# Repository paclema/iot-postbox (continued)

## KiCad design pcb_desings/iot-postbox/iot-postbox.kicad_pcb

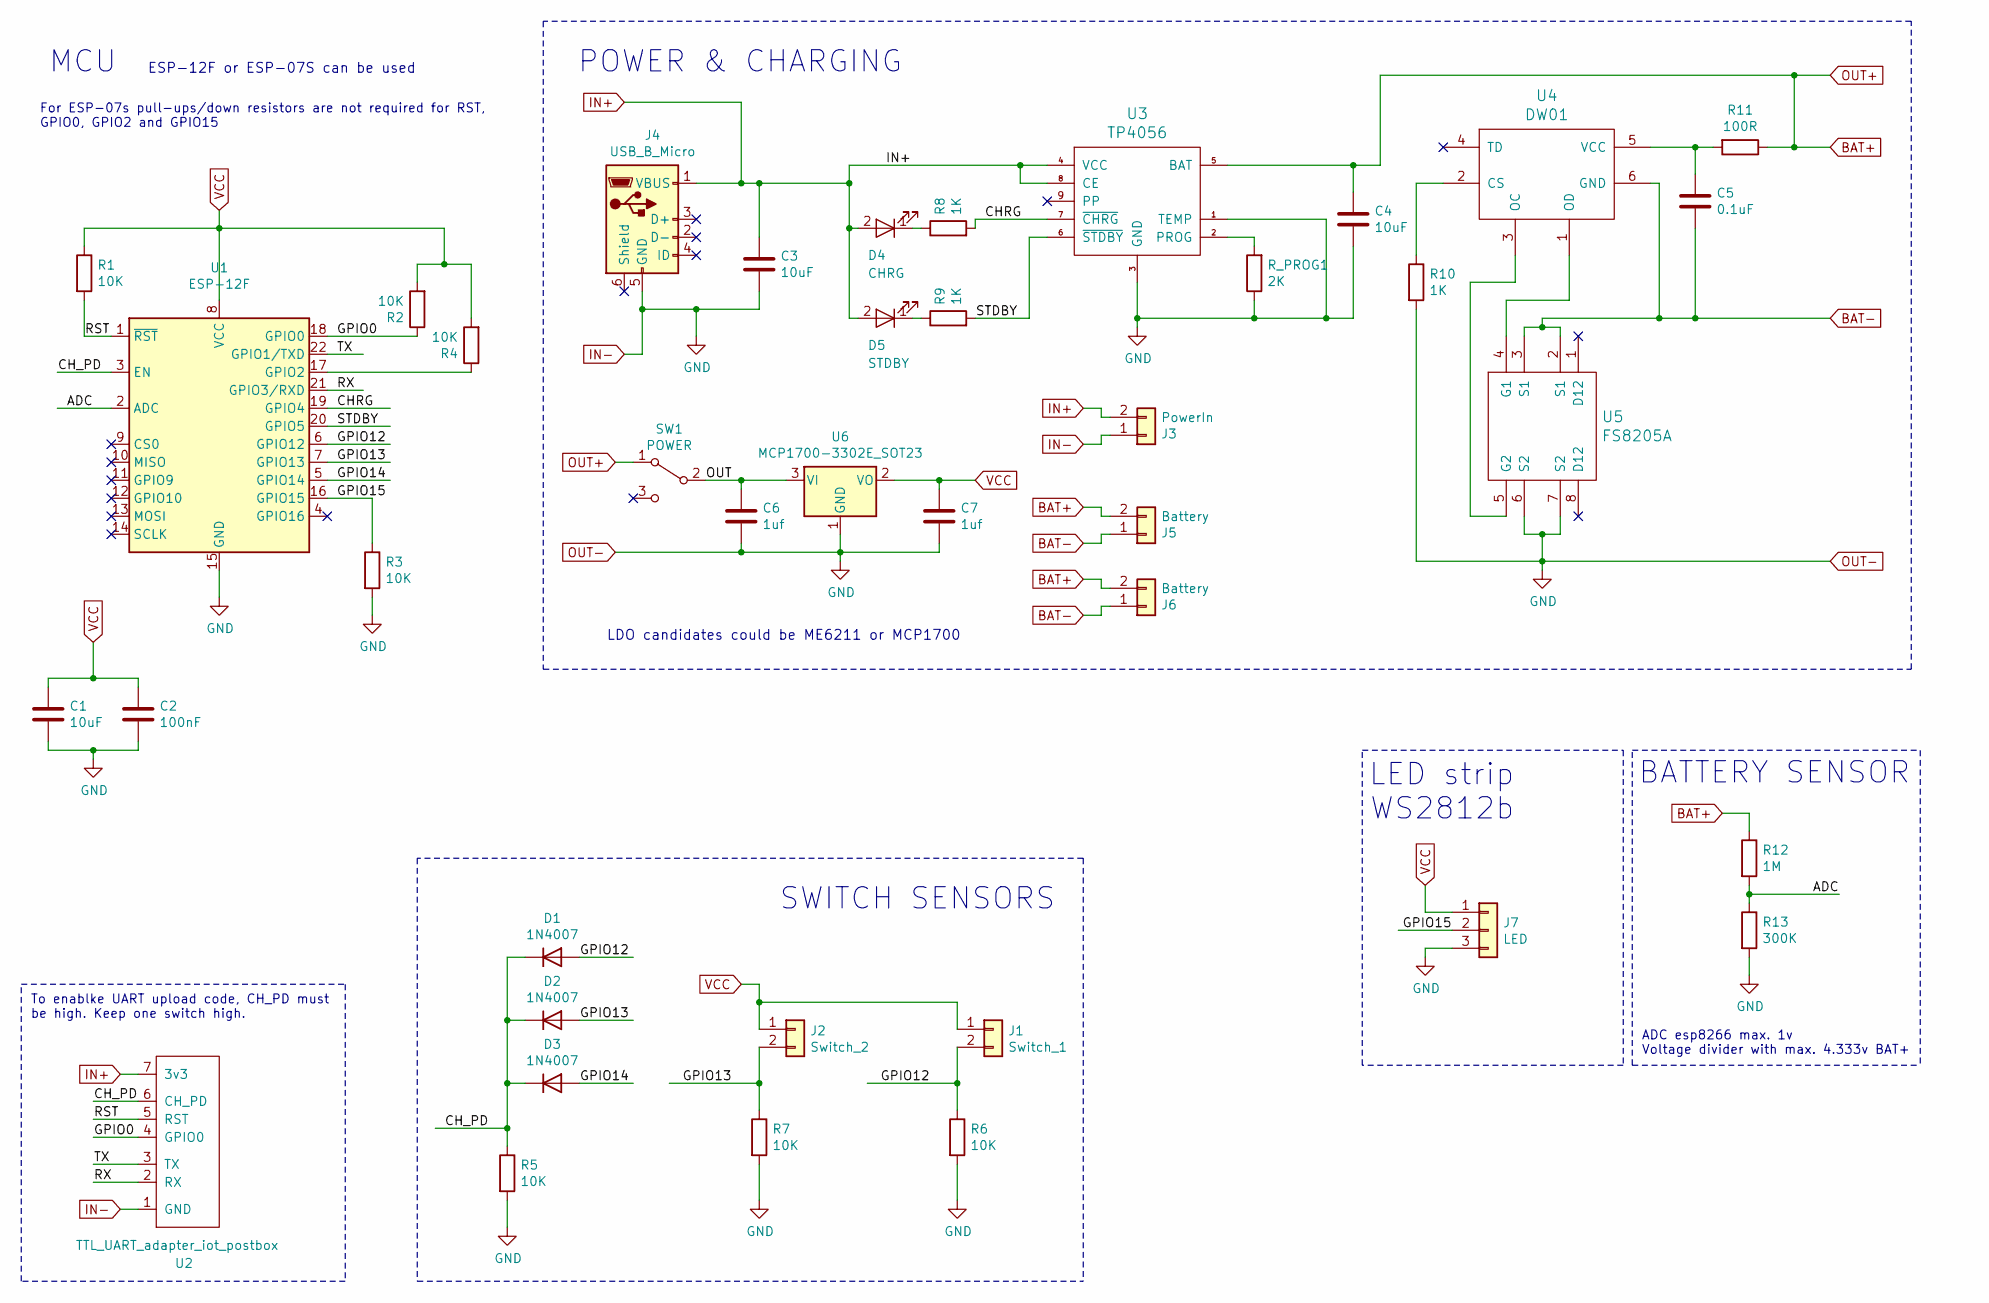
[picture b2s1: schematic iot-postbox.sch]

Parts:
C1, C3, C4: 10uF; C_0805_2012Metric
C2: 100nF; C_0805_2012Metric
C5: 0.1uF; C_0805_2012Metric
C6, C7: 1uf; C_0805_2012Metric
D1, D2, D3: 1N4007; D_SOD-123
D4: CHRG; LED_0805_2012Metric
D5: STDBY; LED_0805_2012Metric
J1: Switch_1; PinHeader_1x02_P2.54mm_Vertical
J2: Switch_2; PinHeader_1x02_P2.54mm_Vertical
J3: PowerIn; PinHeader_1x02_P2.54mm_Vertical
J4: USB_B_Micro; USB_Micro-B_Amphenol_10118194_Horizontal
J5: Battery; JST_PH_S2B-PH-SM4-TB_1x02-1MP_P2.00mm_Horizontal
J6: Battery; PinHeader_1x02_P2.54mm_Vertical
J7: LED; PinHeader_1x03_P2.54mm_Vertical
R1, R2, R3, R4, R5, R6, R7: 10K; R_0805_2012Metric
R8, R9, R10: 1K; R_0805_2012Metric
R11: 100R; R_0805_2012Metric
R12: 1M; R_0805_2012Metric
R13: 300K; R_0805_2012Metric
R_PROG1: 2K; R_0805_2012Metric
SW1: POWER; 1P2T_SPDT_MSK-C02_7pin
U1: ESP-12F; ESP-12E
U2: TTL_UART_adapter_iot_postbox; PinHeader_1x07_P2.54mm_Vertical
U3: TP4056; TP4056_SOP-8-PP
U4: DW01; SOT-23-6_Handsoldering
U5: FS8205A; TSSOP-8_4.4x3mm_P0.65mm
U6: MCP1700-3302E_SOT23; SOT-23

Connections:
/ADC: R12.2, R13.1, U1.2 (ADC)
/CHRG: R8.2, U1.19 (GPIO4), U3.7 (~CHRG)
/CH_PD: D1.1 (K), D2.1 (K), D3.1 (K), R5.1, U1.3 (EN), U2.6 (CH_PD)
/GPIO0: R2.1, U1.18 (GPIO0), U2.4 (GPIO0)
/GPIO12: D1.2 (A), J1.2, R6.1, U1.6 (GPIO12)
/GPIO13: D2.2 (A), J2.2, R7.1, U1.7 (GPIO13)
/GPIO14: D3.2 (A), U1.5 (GPIO14)
/GPIO15: J7.2, R3.1, U1.16 (GPIO15)
/OUT: C6.1, SW1.2 (B), U6.3 (VI)
/RST: R1.2, U1.1 (~RST), U2.5 (RST)
/RX: U1.21 (GPIO3/RXD), U2.2 (RX)
/STDBY: R9.2, U1.20 (GPIO5), U3.6 (~STDBY)
/TX: U1.22 (GPIO1/TXD), U2.3 (TX)
BAT+: C4.1, J5.2, J6.2, R11.1, R12.1, SW1.1 (A), U3.5 (BAT)
BAT-: C5.2, J5.1, J6.1, U4.6 (GND), U5.2 (S1), U5.3 (S1)
IN+: C3.1, D4.2 (A), D5.2 (A), J3.2, J4.1 (VBUS), U2.7 (3v3), U3.4 (VCC), U3.8 (CE)
IN-: C1.2, C2.2, C3.2, C4.2, C6.2, C7.2, J3.1, J4.5 (GND), J7.3, R3.2, R5.2, R6.2, R7.2, R10.2, R13.2, R_PROG1.1, U1.15 (GND), U2.1 (GND), U3.1 (TEMP), U3.3 (GND), U5.6 (S2), U5.7 (S2), U6.1 (GND)
unnamed: C5.1, R11.2, U4.5 (VCC)
unnamed: D4.1 (K), R8.1
unnamed: D5.1 (K), R9.1
unnamed: R4.1, U1.17 (GPIO2)
unnamed: R10.1, U4.2 (CS)
unnamed: R_PROG1.2, U3.2 (PROG)
unnamed: U4.1 (OD), U5.4 (G1)
unnamed: U4.3 (OC), U5.5 (G2)
VCC: C1.1, C2.1, C7.1, J1.1, J2.1, J7.1, R1.1, R2.2, R4.2, U1.8 (VCC), U6.2 (VO)

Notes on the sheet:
To enablke UART upload code, CH_PD must be high. Keep one switch high.
POWER & CHARGING
SWITCH SENSORS
MCU
ESP-12F or ESP-07S can be used
LDO candidates could be ME6211 or MCP1700
ADC esp8266 max. 1v Voltage divider with max. 4.333v BAT+
BATTERY SENSOR
For ESP-07s pull-ups/down resistors are not required for RST, GPIO0, GPIO2 and GPIO15
LED strip WS2812b

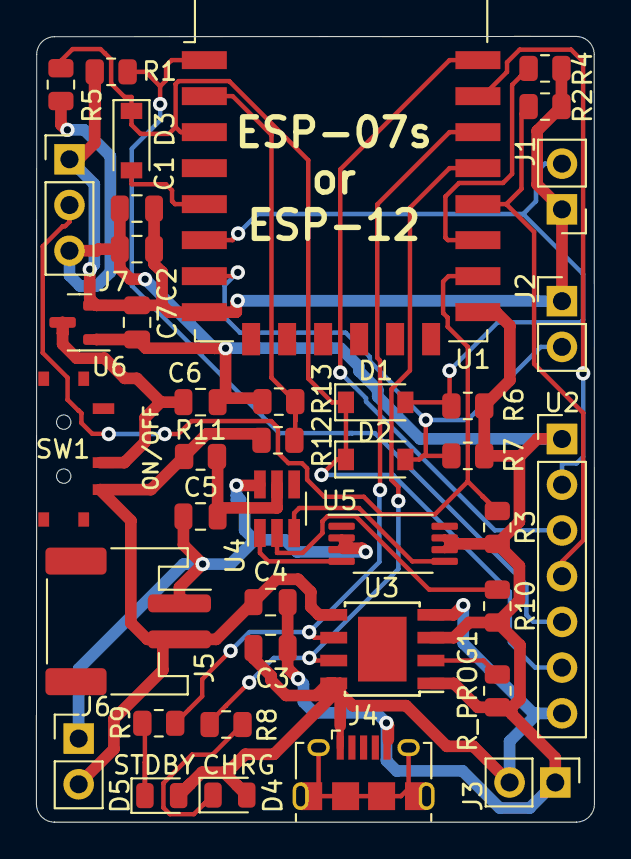
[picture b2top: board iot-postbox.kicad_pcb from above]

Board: 2 copper layers, 31.0 x 43.6 mm, 40 parts (0 on the bottom side), 26 nets.

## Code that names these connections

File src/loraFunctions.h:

#ifndef LoraFunctions_H
#define LoraFunctions_H
#pragma once

#include "Arduino.h"
#include <lmic.h>
#include <hal/hal.h>
#include <SPI.h>


// This EUI must be in little-endian format, so least-significant-byte
// first. When copying an EUI from ttnctl output, this means to reverse
// the bytes. For TTN issued EUIs the last bytes should be 0xD5, 0xB3,
// 0x70.
static const u1_t PROGMEM APPEUI[8]={ 0x00, 0x00, 0x00, 0x00, 0x00, 0x00, 0x00, 0x00 };
void os_getArtEui (u1_t* buf) { memcpy_P(buf, APPEUI, 8);}

// This should also be in little endian format, see above.
static const u1_t PROGMEM DEVEUI[8]={ 0x94, 0xA6, 0x05, 0xD0, 0x7E, 0xD5, 0xB3, 0x70 };
void os_getDevEui (u1_t* buf) { memcpy_P(buf, DEVEUI, 8);}

// This key should be in big endian format (or, since it is not really a
// number but a block of memory, endianness does not really apply). In
// practice, a key taken from ttnctl can be copied as-is.
static const u1_t PROGMEM APPKEY[16] = { 0xB4, 0x7C, 0xF3, 0xC6, 0x8B, 0x22, 0x47, 0x01, 0x13, 0x71, 0x5C, 0x87, 0x0F, 0x96, 0xF2, 0x67 };
void os_getDevKey (u1_t* buf) {  memcpy_P(buf, APPKEY, 16);}

static uint8_t mydata[] = "Hello, world from an iot-postbox_v1 board!";
static osjob_t sendjob;

// Schedule TX every this many seconds (might become longer due to duty
// cycle limitations).
const unsigned TX_INTERVAL = 60;

char TTN_response[30];

class MyHalConfig_t : public Arduino_LMIC::HalConfiguration_t {

public:
  MyHalConfig_t(){};

  // set SPI pins to board configuration, pins may come from pins_arduino.h
  virtual void begin(void) override {
    SPI.begin(RFM95W_SCK_PIN, RFM95W_MISO_PIN, RFM95W_MOSI_PIN, RFM95W_NSS_PIN);
  }
};

static MyHalConfig_t myHalConfig{};
static const lmic_pinmap myPinmap = {
    .nss = RFM95W_NSS_PIN,
    .rxtx = LMIC_UNUSED_PIN,
  	.rst = RFM95W_RESET_PIN,
	.dio = {/*dio0*/ RFM95W_DIO0_PIN, /*dio1*/ RFM95W_DIO1_PIN, /*dio2*/ RFM95W_DIO2_PIN},
    // .rxtx_rx_active = LMIC_UNUSED_PIN,
    // .rssi_cal = 10,
    // .spi_freq = 8000000, // 8MHz
    .pConfig = &myHalConfig
};



void printHex2(unsigned v) {
    v &= 0xff;
    if (v < 16)
        Serial.print('0');
    Serial.print(v, HEX);
}

void do_send(osjob_t* j){
    // Check if there is not a current TX/RX job running
    if (LMIC.opmode & OP_TXRXPEND) {
        Serial.println(F("OP_TXRXPEND, not sending"));
    } else {
        // Prepare upstream data transmission at the next possible time.

        LMIC_setTxData2(1, mydata, sizeof(mydata)-1, 0);
        Serial.println(F("Packet queued"));
    }
    // Next TX is scheduled after TX_COMPLETE event.
}


void onEvent (ev_t ev) {
    Serial.print(os_getTime());
    Serial.print(": ");
    switch(ev) {
        case EV_SCAN_TIMEOUT:
            Serial.println(F("EV_SCAN_TIMEOUT"));
            break;
        case EV_BEACON_FOUND:
            Serial.println(F("EV_BEACON_FOUND"));
            break;
        case EV_BEACON_MISSED:
            Serial.println(F("EV_BEACON_MISSED"));
            break;
        case EV_BEACON_TRACKED:
            Serial.println(F("EV_BEACON_TRACKED"));
            break;
        case EV_JOINING:
            Serial.println(F("EV_JOINING"));
            break;
        case EV_JOINED:
            Serial.println(F("EV_JOINED"));
            {
              u4_t netid = 0;
              devaddr_t devaddr = 0;
              u1_t nwkKey[16];
              u1_t artKey[16];
              LMIC_getSessionKeys(&netid, &devaddr, nwkKey, artKey);
              Serial.print("netid: ");
              Serial.println(netid, DEC);
              Serial.print("devaddr: ");
              Serial.println(devaddr, HEX);
              Serial.print("AppSKey: ");
              for (size_t i=0; i<sizeof(artKey); ++i) {
                if (i != 0)
                  Serial.print("-");
                printHex2(artKey[i]);
              }
              Serial.println("");
              Serial.print("NwkSKey: ");
              for (size_t i=0; i<sizeof(nwkKey); ++i) {
                      if (i != 0)
                              Serial.print("-");
                      printHex2(nwkKey[i]);
              }
              Serial.println();
            }

            // Disable link check validation (automatically enabled
            // during join, but because slow data rates change max TX
	    	// size, we don't use it in this example.
            LMIC_setLinkCheckMode(0);
            break;
        /*
        || This event is defined but not used in the code. No
        || point in wasting codespace on it.
        ||
        || case EV_RFU1:
        ||     Serial.println(F("EV_RFU1"));
        ||     break;
        */
        case EV_JOIN_FAILED:
            Serial.println(F("EV_JOIN_FAILED"));
            break;
        case EV_REJOIN_FAILED:
            Serial.println(F("EV_REJOIN_FAILED"));
            break;
        case EV_TXCOMPLETE:
            Serial.println(F("EV_TXCOMPLETE (includes waiting for RX windows)"));
            if (LMIC.txrxFlags & TXRX_ACK)
              Serial.println(F("Received ack"));
            if (LMIC.dataLen) {
              Serial.print(F("Received "));
              Serial.print(LMIC.dataLen);
              Serial.println(F(" bytes of payload"));
              int i = 0;
              for ( i = 0 ; i < LMIC.dataLen ; i++ )
                TTN_response[i] = LMIC.frame[LMIC.dataBeg+i];
              TTN_response[i] = 0;
			  log_d("LMIC.rssi: %d LMIC.snr: %d TTN_response: %s\n",LMIC.rssi, LMIC.snr, TTN_response);
            
            }
            // Schedule next transmission
            // os_setTimedCallback(&sendjob, os_getTime()+sec2osticks(TX_INTERVAL), do_send);
            break;
        case EV_LOST_TSYNC:
            Serial.println(F("EV_LOST_TSYNC"));
            break;
        case EV_RESET:
            Serial.println(F("EV_RESET"));
            break;
        case EV_RXCOMPLETE:
            // data received in ping slot
            Serial.println(F("EV_RXCOMPLETE"));
            break;
        case EV_LINK_DEAD:
            Serial.println(F("EV_LINK_DEAD"));
            break;
        case EV_LINK_ALIVE:
            Serial.println(F("EV_LINK_ALIVE"));
            break;
        /*
        || This event is defined but not used in the code. No
        || point in wasting codespace on it.
        ||
        || case EV_SCAN_FOUND:
        ||    Serial.println(F("EV_SCAN_FOUND"));
        ||    break;
        */
        case EV_TXSTART:
            Serial.println(F("EV_TXSTART"));
            break;
        case EV_TXCANCELED:
            Serial.println(F("EV_TXCANCELED"));
            break;
        case EV_RXSTART:
            /* do not print anything -- it wrecks timing */
            break;
        case EV_JOIN_TXCOMPLETE:
            Serial.println(F("EV_JOIN_TXCOMPLETE: no JoinAccept"));
            break;

        default:
            Serial.print(F("Unknown event: "));
            Serial.println((unsigned) ev);
            break;
    }
}


void loraSetup(){

	log_d("Setting up lora...");
	// LMIC init
  	os_init_ex(&myPinmap);

	// Reset the MAC state. Session and pending data transfers will be discarded.
    LMIC_reset();

    // Disable link check validation
    // Disable link-check mode and ADR, because ADR tends to complicate testing.
    LMIC_setLinkCheckMode(0);

    // TTN uses SF9 for its RX2 window.
    LMIC.dn2Dr = DR_SF9;

    // Set data rate and transmit power for uplink
    // Set the data rate to Spreading Factor 7.  This is the fastest supported rate for 125 kHz channels, and it
    // minimizes air time and battery power. Set the transmission power to 14 dBi (25 mW).
    // LMIC_setDrTxpow(DR_SF7,14);

    // Start job (sending automatically starts OTAA too)
    // do_send(&sendjob);

	log_d("Setting up lora done");


}

void loraLoop() {
    os_runloop_once();
}
#endif

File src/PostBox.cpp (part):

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
void PostBox::setup(void) {
  #ifndef ARDUINO_IOTPOSTBOX_V1
  // ESP wake Pin, the pin which keeps CH_PD HIGH, a requirement for normal functioning of ESP8266
  pinMode(KEEP_WAKE_PIN, OUTPUT);
  digitalWrite(KEEP_WAKE_PIN, HIGH);
  #else
  pinMode(LDO2_EN_PIN, OUTPUT);
  digitalWrite(LDO2_EN_PIN, HIGH);

  power.setup();
  #endif

  #ifdef USE_TP4056
  pinMode(CHRG_PIN, INPUT);
  pinMode(STDBY_PIN, INPUT);
  #endif

  setupDeepSleep();
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
  publishWakeUp("wakeup");

  Serial.printf(" -- VBAT_STAT_SENSE_PIN: %s --> ChargingStatus: %d\n",  power.getVBatStat() ? "true": "false", chargingStatus);
  Serial.printf(" -- GPIO %d state: %s lastState: %s count: %d\n", sw1.getPin(), sw1.getState() ? "true": "false", sw1.getLastState() ? "true": "false", sw1.getCount());
  Serial.printf(" -- GPIO %d state: %s lastState: %s count: %d\n", sw2.getPin(), sw2.getState() ? "true": "false", sw2.getLastState() ? "true": "false", sw2.getCount());
  Serial.printf(" -- vBus %1.3fmV vBat: %1.3fmV\n", power.vBusSense.mV, power.vBatSense.mV);
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
  fill_solid( leds, NUM_LEDS, CRGB::Black);
  FastLED.show();
  digitalWrite(LDO2_EN_PIN, LOW);
  Serial.println("CH_PD disabled");
  delay(10);

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	#ifdef USE_TP4056
		int sensorValue = analogRead(A0);
		float volts = sensorValue * (4.333 / 1023.0);
		Serial.printf("The internal VCC reads %1.3f volts. CHRG: %d - STDBY: %d\n", volts , !digitalRead(CHRG_PIN), !digitalRead(STDBY_PIN));
	#else
		float volts = ESP.getVcc();
		Serial.printf("The internal VCC reads %1.1f volts\n", volts / 1000);
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void PostBox::turnOffDevice(void) {
  fill_solid( leds, NUM_LEDS, CRGB::Black);
  FastLED.show();
  digitalWrite(LDO2_EN_PIN, LOW);
  Serial.println("CH_PD disabled");
  delay(10);

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

  #ifdef USE_TP4056
  msg_pub = msg_pub + " ,\"chrg\": " + !digitalRead(CHRG_PIN);
  msg_pub = msg_pub + " ,\"stdby\": " + !digitalRead(STDBY_PIN);
  #endif
  msg_pub +=" }";

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
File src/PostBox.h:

#ifndef PostBox_H
#define PostBox_H

#pragma once
#include <Arduino.h>

#ifdef ESP32
#include <esp_wifi.h>
#include <WiFi.h>

//Power Management and ADC sense inputs
// ------------------------------------
#include "PowerManagement.h"

#endif


#include <MQTTClient.h>


// WS2812B LED strip
// -----------------
#include <FastLED.h>

#ifdef ARDUINO_IOTPOSTBOX_V1
  #define LED_PIN    PIN_NEOPIXEL 	//GPIO17
#else
  #define LED_PIN    15 			//GPIO15
#endif

#define NUM_LEDS  4
#define BRIGHTNESS 10


// PostBoxSwitch sensors
// ---------------------
#include "PostBoxSwitch.h"
#ifndef ARDUINO_IOTPOSTBOX_V1
  #define SW1_PIN         12
  #define SW2_PIN         13
  #define KEEP_WAKE_PIN   14    // Pin which is used to Keep ESP awake until job is finished
#endif


// PostBox sleep configs
// ---------------------
#define WAKE_UP_BITMASK ( GPIO_NUM_4 | GPIO_NUM_5 )
RTC_DATA_ATTR static int bootCount = 0;


// Battery charger feedback
// ------------------------
#ifdef ARDUINO_IOTPOSTBOX_V1
//TODO: BATTERY, USB POWER AND CHARGING SENSE

#else
//Using tp4056 charger with battery fedback to ADC0 (max 1v! for ESP8266) and tp4056 chrg and stdby pins feedback:
  #define USE_TP4056
  #define NO_SLEEP_WHILE_CHARGING    // While charging the ESP won't go to sleep. Comment out this line if you want to avoid that

  #ifdef USE_TP4056
    #define CHRG_PIN    4    // Pin for charge battery. LOW when usb is connected and baterry is being charged.
    #define STDBY_PIN   5    // Pin for stdby battery charge. LOW for battery charge termination.
  #else
    ADC_MODE(ADC_VCC);          // Allows to monitor the internal VCC level; it varies with WiFi load
  #endif
#endif


class PostBox {
public:
	CRGB leds[NUM_LEDS];

	PostBoxSwitch sw1;
	PostBoxSwitch sw2;


	String MQTTBaseTopic;
	MQTTClient *mqtt;

	PowerManagement power;
	PowerStatus powerStatus = PowerStatus::Unknown;
	ChargingStatus chargingStatus = ChargingStatus::Unknown;


	PostBox(void);
	~PostBox(void);

	void setup(void);
	void init(void);
	void loop(void);
	void powerOff(void);

	void updatePowerStatus(void);

	float readVoltage(void);
	float getVBus(void) { return power.vBusSense.mV;};
	float getVBat(void) { return power.vBatSense.mV;};
	float getVBatNow(void) { return power.vBatSense.getLastmV(); };
	float getVBatStat(void) { return power.getVBatStat();};
	ChargingStatus getChargingStatus(void) { return chargingStatus;};
	PowerStatus getPowerStatus(void) { return powerStatus;};
	bool isWakeUpPublished(void) { return wakeUpPublished;};



	void updateLedStrip(void);

	void printWakeupReason(void);
	void setupDeepSleep(void);
	void turnOffDevice(void);

	void publishWakeUp(String topic_end);

	void setMQTTBaseTopic(String topic) { MQTTBaseTopic = topic; }
	void setMQTTClient(MQTTClient * client) { mqtt = client; }



private:

	bool wakeUpPublished = false;
	int wakeUpGPIO = -1;              // Variable to store the GPIO which triggered the wake from Deep Sleep


};

#endif

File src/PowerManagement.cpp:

#include "PowerManagement.h"

PowerManagement::PowerManagement(void) : 
  vBusSense(VBUS_SENSE_PIN, VBUS_ADC_CHANNEL, (float)VBUS_VOLTAGE_DIVIDER_COEFICIENT, "VBUS"),
  vBatSense(VBAT_SENSE_PIN, VBAT_ADC_CHANNEL, (float)VBAT_VOLTAGE_DIVIDER_COEFICIENT, "VBAT")
{


}


PowerManagement::~PowerManagement(void) {
}


void PowerManagement::setup(void){
	vBusSense.setup(VBUS_ADC_ATTEN);
	vBatSense.setup(VBAT_ADC_ATTEN);
	pinMode(VBAT_STAT_SENSE_PIN, INPUT);
	attachInterrupt(VBAT_STAT_SENSE_PIN, std::bind(&PowerManagement::isrCharging,this), CHANGE);
}


void PowerManagement::update(void){
	//Read ADCSense pins
  	vBusSense.updatedADC();
	vBatSense.updatedADC();
	vBatStat = digitalRead(VBAT_STAT_SENSE_PIN);

	lastPowerStatus = powerStatus;
	// Charging always happens if vBus > 3,75v for MCP73831/2, 4v for TP4056
	// if (vBusSense.mV >= VBUS_MIN){
	if (vBusSense.mV >= 4000){
	if (vBatStat == LOW) {
		chargingStatus = ChargingStatus::Charging;
		lastChargingStatus = chargingStatus;
		powerStatus = PowerStatus::BatteryAndUSBPowered;
	} else if (vBatStat == HIGH) {
		if (lastChargingStatus ==  ChargingStatus::Charging) {
		chargingStatus = ChargingStatus::Charged;
		lastChargingStatus = chargingStatus;
		powerStatus = PowerStatus::BatteryAndUSBPowered;
		} else if (lastChargingStatus !=  ChargingStatus::Charging) {
		chargingStatus = ChargingStatus::NotCharging;
		powerStatus = PowerStatus::USBPowered;
		}
	} else chargingStatus = ChargingStatus::Unknown;

	// } else if (vBusSense.mV <= VBUS_MIN-1) {
	} else if (vBusSense.mV <= 3999) {
	chargingStatus = ChargingStatus::NotCharging;
	lastChargingStatus = chargingStatus;
	// if (vBatSense.mV >= VBAT_MIN){
	if (vBatSense.mV >= 2700){
		powerStatus = PowerStatus::BatteryPowered;
	} else if (vBatSense.mV <= 100) powerStatus = PowerStatus::USBPowered;
	}

}

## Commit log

2021-12-20 Added PostBoxSwitch struct instead button array
2021-12-20 Fixed first wakeup mqtt publish msg
2021-12-20 Added WS2812b support for Switch_2
2021-12-20 Fixed switch counter and led strip feature
2021-12-21 Update platformio default targets
2021-12-21 Removed wemos submodule
2021-12-21 Updated iot-postbox sch and pcb to v0.2 correcting Switch references
2021-12-21 Exported pcb iot-postbox v0.3. Added ws2812b led strip to sch and pcb
2021-12-21 Moved docs pic for v0.0
2022-03-24 Added Espressif kicad libs submodule and Kicad files for iot-postobox_v1
2022-06-09 Added iot-postbox v1.0 hardware designs
2022-06-09 Fixed PostBoxSwitch struct to make it compatible with esp32
2022-06-10 Add mhetesp32devkit_stable platformio target
2022-06-10 Updated PCB desings readme
2022-06-10 small fix readme
2022-06-14 Added iot-postbox_v1 sch to v1.1. Added minor documentation
2022-06-14 Ported fw to handle old and new iot-postbox boards. Added PostBoxSwitch class with SW interrupts
2022-06-15 Added esp32s2 deepsleep functions
2022-06-15 Added temporary platform packages to iot-postbox_v1 platformio target
2022-06-15 Added PostBox class
2022-06-20 Added PostBox missing functions and instanced objec at main
2022-06-24 Removed unnecesary constructor
2022-06-24 Added test adc functions
2022-06-24 Cleaned main
2022-06-26 Cleaned ADC functions
2022-06-27 Enabled adc calibration and added debug
2022-06-28 Added adc calibration and average for vBat and debug thorugh webconfigserver dashboard
2022-07-01 Improved power and charging status recognition
2022-07-01 Removed waitting for serial at setup
2022-07-01 Changed led strip instance as fastled object insted adafruit neopixel and fixed power and charging states
2022-07-02 Increased dashboard float plot values round to more decimals
2022-07-02 INproved power status initialization and loop update
2022-07-02 Fixed fastled lib dependency
2022-07-02 Improved loop slep reducing fastled show calls only by status change
2022-07-02 Added charging circuit test findings
2022-07-02 Fixed wakeUp mask and gpio reason report
2022-07-03 Increased vcc mqtt payload decimal precision to 3 digits
2022-07-03 Added bott counter at mqtt payload
2022-07-07 Updated iboom. Upgraded ADC array to 30 measures. Added IoT-PostBox_v1_4MB target
2022-07-07 Added some sch info
2022-07-07 Added lora example
2022-07-08 Added PowerStatus and ChargingStatus to publish payload
2022-07-08 Added vBat and vBus to publish payload
2022-07-08 Add vBat and vBus to publish payload and increase buffer dinamically
2022-07-08 Changed vBus min consider charge voltage to 4v
2022-07-10 Added ADCSense class and moved vBat sense use as its instance
2022-07-10 Added vBus as ADCSense object and cleaned ADCSense constructor
2022-07-10 Removed old adc sense variables
2022-07-12 Added PowerManagement class to handle power status, ADCSense and vBatStat inputs
2022-07-12 Added PowerManagement lib and removed old classes
2022-07-15 Fixed IoT-PostBox_v1 partition table
2023-02-15 Added loraFunctrions using custom SPI pinout
2023-02-16 Fixed Lora module pin mapping
2023-02-16 Publish TTN when publish on wakeup mqtt topic
2023-02-16 Added Cayenne payload
2023-03-10 Added windows driver docs and configured pio with littlefs filesystem
2023-04-04 Added lora payload custom decoder
2023-04-04 Replaced lora cayenne payload to custom
2023-04-05 Removed waiting for serial
2023-04-05 Updated MQTT payload. Replaced GPIO_# with sw1 and sw2 counter and state objects. Changed rssi to rssi_STA
2025-07-31 Add hardware doc files for v0.3
2025-07-31 Add hardware doc files for ttl_to_usb_adapter board
2025-07-31 Move iot-postbox v1.0 bom and doc files to the correct location
2025-07-31 Created iot-postbox v1.2 migrating to kicad v9. Fixed missing 3d designs, replaced horizontal footprints for some connectors.
2025-07-31 Export iot-postbox v1.2 hardware bom, gerber and doc files
2025-07-31 Fix pcb_desing readme.md with correct images for latest v1.2 version
2025-08-01 Remove obsolete panelized iot_postbox_v0.0 files from PCB designs
2025-08-01 Update readme for IoT-PostBox PCB designs, including detailed descriptions of hardware functionality, features, and version comparisons.
2025-08-01 Deleted deprecated webserver. Use now WebConfigServer default webserver
2025-08-01 Refactor README.md to update project description, installation instructions, and web dashboard details for IoT-PostBox.
2025-08-01 Add license section and donation links to README.md
2025-08-01 Add LICENSE.md file with Creative Commons licensing information
2025-08-01 Fix README.md for clarity and accuracy in hardware evolution and link to PCB designs
2025-08-03 Add ibom for IoT-PostBox v0.3
2025-08-03 Renamed schematic PDF for IoT-PostBox v1.2
2025-08-03 Update readme for IoT-PostBox hardware documentation
2025-09-26 Fix wake-up bitmask definition in PostBox.h for correct GPIO usage with ESP-IDF v5
2025-09-26 Replace PubSubClient with MQTTClient v1.1.0. Bump WebConfigServer, PowerManagement, FastLED and MCCI LoRaWAN LMIC library to latest tested versions
2025-09-26 Add IoT-PostBox v1 board variant files and upgrade pio env configuration
2025-09-26 Add IoT-PostBox 4MB version board variant files and update platformio target configuration
